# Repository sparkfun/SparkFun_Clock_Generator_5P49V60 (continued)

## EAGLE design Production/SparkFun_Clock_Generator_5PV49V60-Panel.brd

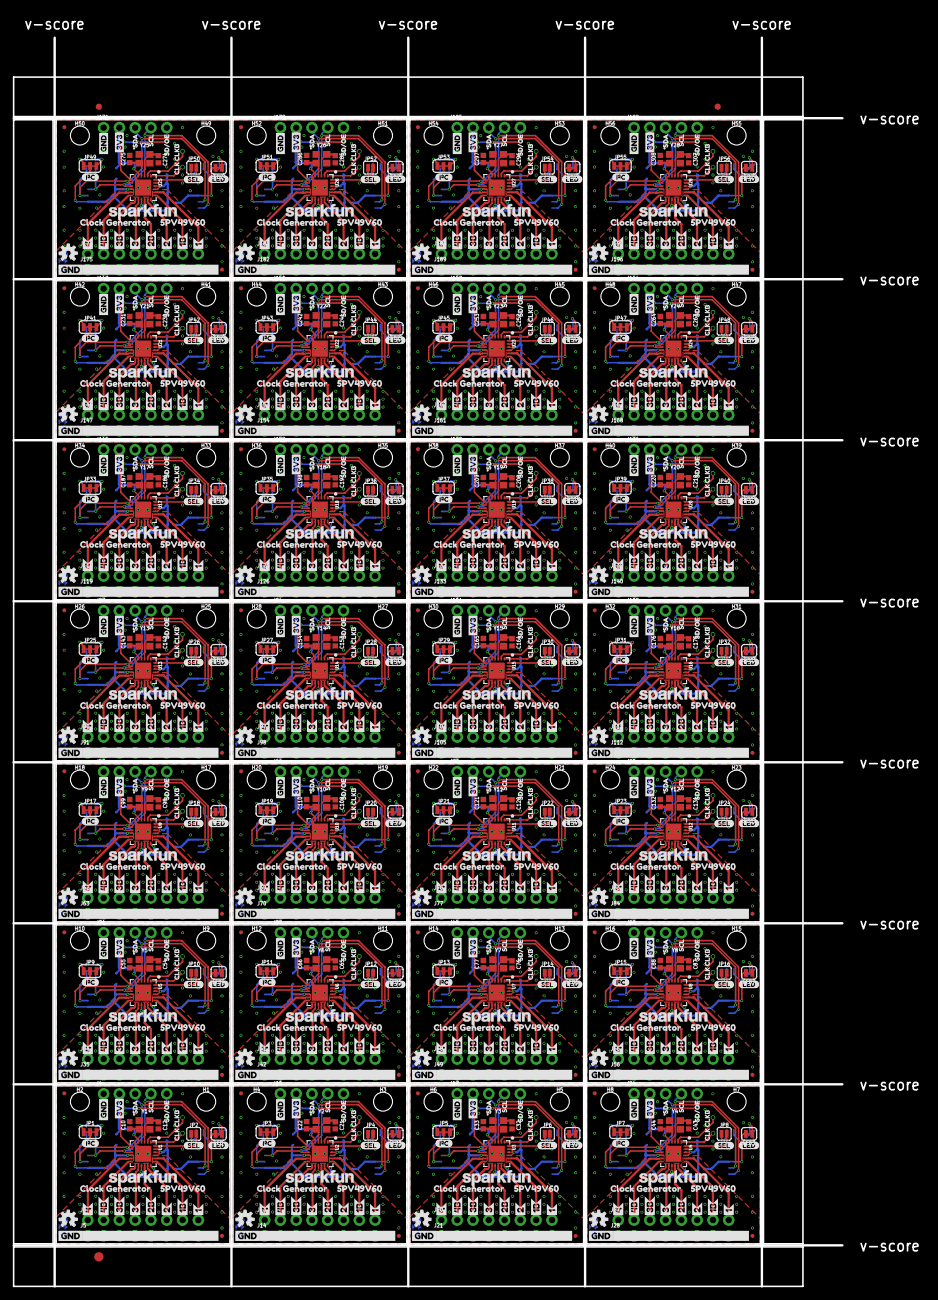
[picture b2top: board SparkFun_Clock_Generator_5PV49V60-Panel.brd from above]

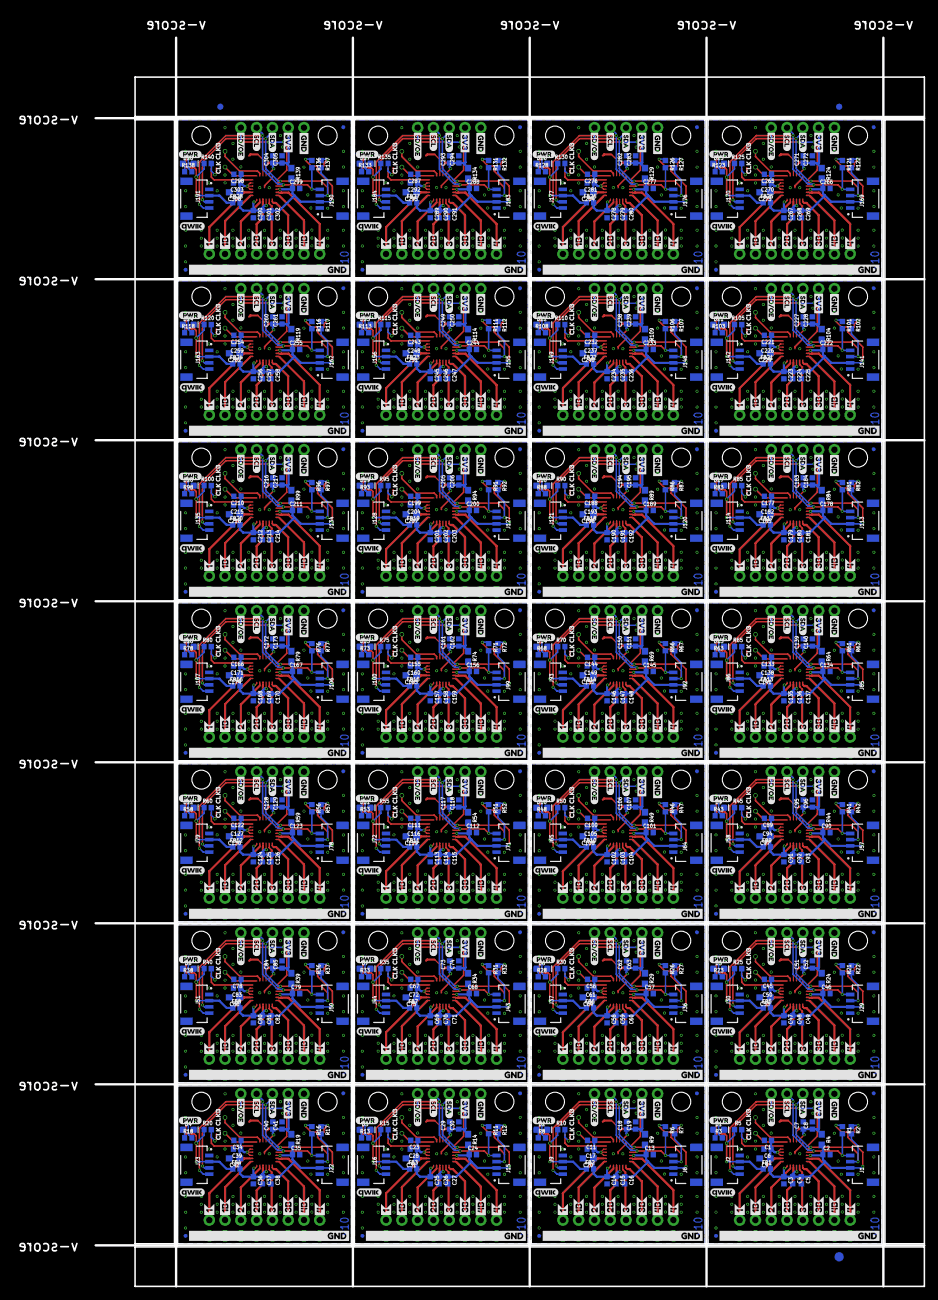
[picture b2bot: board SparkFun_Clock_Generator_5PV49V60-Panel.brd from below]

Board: 2 copper layers, 133.3 x 200.9 mm, 2162 parts (1067 on the bottom side), 644 nets.

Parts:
C1, C2, C3, C4, C5, C6, C7, C11, C13, C14, C15, C16, C17, C18, C23, C24, C25, C26, C27, C28, C29, C34, C35, C36, C37, C38, C39, C40, C45, C46, C47, C48, C49, C50, C51, C56, C57, C58, C59, C60, C61, C62, C67, C68, C69, C70, C71, C72, C73, C78, C79, C80, C81, C82, C83, C84, C89, C90, C91, C92, C93, C94, C95, C100, C101, C102, C103, C104, C105, C106, C111, C112, C113, C114, C115, C116, C117, C122, C123, C124, C125, C126, C127, C128, C133, C134, C135, C136, C137, C138, C139, C144, C145, C146, C147, C148, C149, C150, C155, C156, C157, C158, C159, C160, C161, C166, C167, C168, C169, C170, C171, C172, C177, C178, C179, C180, C181, C182, C183, C188, C189, C190, C191, C192, C193, C194, C199, C200, C201, C202, C203, C204, C205, C210, C211, C212, C213, C214, C215, C216, C221, C222, C223, C224, C225, C226, C227, C232, C233, C234, C235, C236, C237, C238, C243, C244, C245, C246, C247, C248, C249, C254, C255, C256, C257, C258, C259, C260, C265, C266, C267, C268, C269, C270, C271, C276, C277, C278, C279, C280, C281, C282, C287, C288, C289, C290, C291, C292, C293, C298, C299, C300, C301, C302, C303, C304: 0.1uF; 0402
C8, C19, C30, C41, C52, C63, C74, C85, C96, C107, C118, C129, C140, C151, C162, C173, C184, C195, C206, C217, C228, C239, C250, C261, C272, C283, C294, C305: 1.0uF; 0402
C9, C20, C31, C42, C53, C64, C75, C86, C97, C108, C119, C130, C141, C152, C163, C174, C185, C196, C207, C218, C229, C240, C251, C262, C273, C284, C295, C306: 10uF; 0603
C10, C12, C21, C22, C32, C33, C43, C44, C54, C55, C65, C66, C76, C77, C87, C88, C98, C99, C109, C110, C120, C121, C131, C132, C142, C143, C153, C154, C164, C165, C175, C176, C186, C187, C197, C198, C208, C209, C219, C220, C230, C231, C241, C242, C252, C253, C263, C264, C274, C275, C285, C286, C296, C297, C307, C308: 12pF; 0402
D1, D2, D3, D4, D5, D6, D7, D8, D9, D10, D11, D12, D13, D14, D15, D16, D17, D18, D19, D20, D21, D22, D23, D24, D25, D26, D27, D28: RED; LED-0603
E$1, E$2, E$3, E$4: FIDUCIAL-1X2
E$5, E$6: FIDUCIAL-1.5X3
FB1, FB2, FB3, FB4, FB5, FB6, FB7, FB8, FB9, FB10, FB11, FB12, FB13, FB14, FB15, FB16, FB17, FB18, FB19, FB20, FB21, FB22, FB23, FB24, FB25, FB26, FB27, FB28: FERRITE_BEAD-120_OHM-0402; 0402
FD1, FD2, FD3, FD4, FD5, FD6, FD7, FD8, FD9, FD10, FD11, FD12, FD13, FD14, FD15, FD16, FD17, FD18, FD19, FD20, FD21, FD22, FD23, FD24, FD25, FD26, FD27, FD28, FD29, FD30, FD31, FD32, FD33, FD34, FD35, FD36, FD37, FD38, FD39, FD40, FD41, FD42, FD43, FD44, FD45, FD46, FD47, FD48, FD49, FD50, FD51, FD52, FD53, FD54, FD55, FD56, FD57, FD58, FD59, FD60, FD61, FD62, FD63, FD64, FD65, FD66, FD67, FD68, FD69, FD70, FD71, FD72, FD73, FD74, FD75, FD76, FD77, FD78, FD79, FD80, FD81, FD82, FD83, FD84, FD85, FD86, FD87, FD88, FD89, FD90, FD91, FD92, FD93, FD94, FD95, FD96, FD97, FD98, FD99, FD100, FD101, FD102, FD103, FD104, FD105, FD106, FD107, FD108, FD109, FD110, FD111, FD112: FIDUCIALUFIDUCIAL; FIDUCIAL-MICRO
H1, H2, H3, H4, H5, H6, H7, H8, H9, H10, H11, H12, H13, H14, H15, H16, H17, H18, H19, H20, H21, H22, H23, H24, H25, H26, H27, H28, H29, H30, H31, H32, H33, H34, H35, H36, H37, H38, H39, H40, H41, H42, H43, H44, H45, H46, H47, H48, H49, H50, H51, H52, H53, H54, H55, H56: STAND-OFFTIGHT; STAND-OFF-TIGHT
J1, J2, J6, J9, J15, J16, J22, J23, J29, J30, J36, J37, J43, J44, J50, J51, J57, J58, J64, J65, J71, J72, J78, J79, J85, J86, J92, J93, J99, J100, J106, J107, J113, J114, J120, J121, J127, J128, J134, J135, J141, J142, J148, J149, J155, J156, J162, J163, J169, J170, J176, J177, J183, J184, J190, J191: QWIIC_RIGHT_ANGLE; JST04_1MM_RA
J3, J5, J13, J14, J20, J21, J27, J28, J34, J35, J41, J42, J48, J49, J55, J56, J62, J63, J69, J70, J76, J77, J83, J84, J90, J91, J97, J98, J104, J105, J111, J112, J118, J119, J125, J126, J132, J133, J139, J140, J146, J147, J153, J154, J160, J161, J167, J168, J174, J175, J181, J182, J188, J189, J195, J196: 1X08_NO_SILK
J4, J10, J17, J24, J31, J38, J45, J52, J59, J66, J73, J80, J87, J94, J101, J108, J115, J122, J129, J136, J143, J150, J157, J164, J171, J178, J185, J192: 1X05_NO_SILK
J7, J8, J11, J12, J18, J19, J25, J26, J32, J33, J39, J40, J46, J47, J53, J54, J60, J61, J67, J68, J74, J75, J81, J82, J88, J89, J95, J96, J102, J103, J109, J110, J116, J117, J123, J124, J130, J131, J137, J138, J144, J145, J151, J152, J158, J159, J165, J166, J172, J173, J179, J180, J186, J187, J193, J194: 1X01_SMALL
JP1, JP3, JP5, JP7, JP9, JP11, JP13, JP15, JP17, JP19, JP21, JP23, JP25, JP27, JP29, JP31, JP33, JP35, JP37, JP39, JP41, JP43, JP45, JP47, JP49, JP51, JP53, JP55: JUMPER-SMT_3_2-NC_TRACE_SILK; SMT-JUMPER_3_2-NC_TRACE_SILK
JP2, JP4, JP6, JP8, JP10, JP12, JP14, JP16, JP18, JP20, JP22, JP24, JP26, JP28, JP30, JP32, JP34, JP36, JP38, JP40, JP42, JP44, JP46, JP48, JP50, JP52, JP54, JP56: JUMPER-SMT_2_NO_SILK; SMT-JUMPER_2_NO_SILK
LED, LED1, LED2, LED3, LED4, LED5, LED6, LED7, LED8, LED9, LED10, LED11, LED12, LED13, LED14, LED15, LED16, LED17, LED18, LED19, LED20, LED21, LED22, LED23, LED24, LED25, LED26, LED27: JUMPER-SMT_2_NC_TRACE_SILK; SMT-JUMPER_2_NC_TRACE_SILK
LOGO1, LOGO4, LOGO7, LOGO10, LOGO13, LOGO16, LOGO19, LOGO22, LOGO25, LOGO28, LOGO31, LOGO34, LOGO37, LOGO40, LOGO43, LOGO46, LOGO49, LOGO52, LOGO55, LOGO58, LOGO61, LOGO64, LOGO67, LOGO70, LOGO73, LOGO76, LOGO79, LOGO82: SFE_LOGO_NAME.1_INCH; SFE_LOGO_NAME_.1
LOGO2, LOGO5, LOGO8, LOGO11, LOGO14, LOGO17, LOGO20, LOGO23, LOGO26, LOGO29, LOGO32, LOGO35, LOGO38, LOGO41, LOGO44, LOGO47, LOGO50, LOGO53, LOGO56, LOGO59, LOGO62, LOGO65, LOGO68, LOGO71, LOGO74, LOGO77, LOGO80, LOGO83: OSHW-LOGOS; OSHW-LOGO-S
LOGO3, LOGO6, LOGO9, LOGO12, LOGO15, LOGO18, LOGO21, LOGO24, LOGO27, LOGO30, LOGO33, LOGO36, LOGO39, LOGO42, LOGO45, LOGO48, LOGO51, LOGO54, LOGO57, LOGO60, LOGO63, LOGO66, LOGO69, LOGO72, LOGO75, LOGO78, LOGO81, LOGO84: QWIIC_LOGO_4MM; QWIIC_4MM
R1, R2, R5, R6, R7, R10, R11, R12, R15, R16, R17, R20, R21, R22, R25, R26, R27, R30, R31, R32, R35, R36, R37, R40, R41, R42, R45, R46, R47, R50, R51, R52, R55, R56, R57, R60, R61, R62, R65, R66, R67, R70, R71, R72, R75, R76, R77, R80, R81, R82, R85, R86, R87, R90, R91, R92, R95, R96, R97, R100, R101, R102, R105, R106, R107, R110, R111, R112, R115, R116, R117, R120, R121, R122, R125, R126, R127, R130, R131, R132, R135, R136, R137, R140: 10k; 0402
R3, R8, R13, R18, R23, R28, R33, R38, R43, R48, R53, R58, R63, R68, R73, R78, R83, R88, R93, R98, R103, R108, R113, R118, R123, R128, R133, R138: 1KOHM-0402-1/16W-1%; 0402
R4, R9, R14, R19, R24, R29, R34, R39, R44, R49, R54, R59, R64, R69, R74, R79, R84, R89, R94, R99, R104, R109, R114, R119, R124, R129, R134, R139: 2.2; 0603
U1, U2, U3, U4, U5, U6, U7, U8, U9, U10, U11, U12, U13, U14, U15, U16, U17, U18, U19, U20, U21, U22, U23, U24, U25, U26, U27, U28: IDT_5P49V60_CLOCK_GENERATOR; VFQFPN-24
U$1, U$76, U$114, U$152, U$190, U$228, U$266, U$304, U$342, U$380, U$418, U$456, U$494, U$532, U$570, U$608, U$646, U$684, U$722, U$760, U$798, U$836, U$874, U$912, U$950, U$988, U$1026, U$1064: SEL0
U$2, U$18, U$39, U$47, U$77, U$85, U$115, U$123, U$153, U$161, U$191, U$199, U$229, U$237, U$267, U$275, U$305, U$313, U$343, U$351, U$381, U$389, U$419, U$427, U$457, U$465, U$495, U$503, U$533, U$541, U$571, U$579, U$609, U$617, U$647, U$655, U$685, U$693, U$723, U$731, U$761, U$769, U$799, U$807, U$837, U$845, U$875, U$883, U$913, U$921, U$951, U$959, U$989, U$997, U$1027, U$1035: 3V3-03
U$3, U$19, U$40, U$48, U$78, U$86, U$116, U$124, U$154, U$162, U$192, U$200, U$230, U$238, U$268, U$276, U$306, U$314, U$344, U$352, U$382, U$390, U$420, U$428, U$458, U$466, U$496, U$504, U$534, U$542, U$572, U$580, U$610, U$618, U$648, U$656, U$686, U$694, U$724, U$732, U$762, U$770, U$800, U$808, U$838, U$846, U$876, U$884, U$914, U$922, U$952, U$960, U$990, U$998, U$1028, U$1036: GND-03
U$4, U$41, U$79, U$117, U$155, U$193, U$231, U$269, U$307, U$345, U$383, U$421, U$459, U$497, U$535, U$573, U$611, U$649, U$687, U$725, U$763, U$801, U$839, U$877, U$915, U$953, U$991, U$1029: PWR-()-03
U$5, U$42, U$80, U$118, U$156, U$194, U$232, U$270, U$308, U$346, U$384, U$422, U$460, U$498, U$536, U$574, U$612, U$650, U$688, U$726, U$764, U$802, U$840, U$878, U$916, U$954, U$992, U$1030: SDA11
U$6, U$43, U$81, U$119, U$157, U$195, U$233, U$271, U$309, U$347, U$385, U$423, U$461, U$499, U$537, U$575, U$613, U$651, U$689, U$727, U$765, U$803, U$841, U$879, U$917, U$955, U$993, U$1031: SCL10
U$7, U$44, U$82, U$120, U$158, U$196, U$234, U$272, U$310, U$348, U$386, U$424, U$462, U$500, U$538, U$576, U$614, U$652, U$690, U$728, U$766, U$804, U$842, U$880, U$918, U$956, U$994, U$1032: SD#OE12
U$8, U$38, U$65, U$68, U$103, U$106, U$141, U$144, U$179, U$182, U$217, U$220, U$255, U$258, U$293, U$296, U$331, U$334, U$369, U$372, U$407, U$410, U$445, U$448, U$483, U$486, U$521, U$524, U$559, U$562, U$597, U$600, U$635, U$638, U$673, U$676, U$711, U$714, U$749, U$752, U$787, U$790, U$825, U$828, U$863, U$866, U$901, U$904, U$939, U$942, U$977, U$980, U$1015, U$1018, U$1053, U$1056: 46
U$9, U$25, U$61, U$69, U$99, U$107, U$137, U$145, U$175, U$183, U$213, U$221, U$251, U$259, U$289, U$297, U$327, U$335, U$365, U$373, U$403, U$411, U$441, U$449, U$479, U$487, U$517, U$525, U$555, U$563, U$593, U$601, U$631, U$639, U$669, U$677, U$707, U$715, U$745, U$753, U$783, U$791, U$821, U$829, U$859, U$867, U$897, U$905, U$935, U$943, U$973, U$981, U$1011, U$1019, U$1049, U$1057: 4B7
U$10, U$24, U$60, U$70, U$98, U$108, U$136, U$146, U$174, U$184, U$212, U$222, U$250, U$260, U$288, U$298, U$326, U$336, U$364, U$374, U$402, U$412, U$440, U$450, U$478, U$488, U$516, U$526, U$554, U$564, U$592, U$602, U$630, U$640, U$668, U$678, U$706, U$716, U$744, U$754, U$782, U$792, U$820, U$830, U$858, U$868, U$896, U$906, U$934, U$944, U$972, U$982, U$1010, U$1020, U$1048, U$1058: 3B5
U$11, U$37, U$64, U$71, U$102, U$109, U$140, U$147, U$178, U$185, U$216, U$223, U$254, U$261, U$292, U$299, U$330, U$337, U$368, U$375, U$406, U$413, U$444, U$451, U$482, U$489, U$520, U$527, U$558, U$565, U$596, U$603, U$634, U$641, U$672, U$679, U$710, U$717, U$748, U$755, U$786, U$793, U$824, U$831, U$862, U$869, U$900, U$907, U$938, U$945, U$976, U$983, U$1014, U$1021, U$1052, U$1059: 34
U$12, U$23, U$59, U$72, U$97, U$110, U$135, U$148, U$173, U$186, U$211, U$224, U$249, U$262, U$287, U$300, U$325, U$338, U$363, U$376, U$401, U$414, U$439, U$452, U$477, U$490, U$515, U$528, U$553, U$566, U$591, U$604, U$629, U$642, U$667, U$680, U$705, U$718, U$743, U$756, U$781, U$794, U$819, U$832, U$857, U$870, U$895, U$908, U$933, U$946, U$971, U$984, U$1009, U$1022, U$1047, U$1060: 2B3
U$13, U$27, U$63, U$73, U$101, U$111, U$139, U$149, U$177, U$187, U$215, U$225, U$253, U$263, U$291, U$301, U$329, U$339, U$367, U$377, U$405, U$415, U$443, U$453, U$481, U$491, U$519, U$529, U$557, U$567, U$595, U$605, U$633, U$643, U$671, U$681, U$709, U$719, U$747, U$757, U$785, U$795, U$823, U$833, U$861, U$871, U$899, U$909, U$937, U$947, U$975, U$985, U$1013, U$1023, U$1051, U$1061: 22
U$14, U$22, U$58, U$74, U$96, U$112, U$134, U$150, U$172, U$188, U$210, U$226, U$248, U$264, U$286, U$302, U$324, U$340, U$362, U$378, U$400, U$416, U$438, U$454, U$476, U$492, U$514, U$530, U$552, U$568, U$590, U$606, U$628, U$644, U$666, U$682, U$704, U$720, U$742, U$758, U$780, U$796, U$818, U$834, U$856, U$872, U$894, U$910, U$932, U$948, U$970, U$986, U$1008, U$1024, U$1046, U$1062: 1B1
U$15, U$26, U$62, U$75, U$100, U$113, U$138, U$151, U$176, U$189, U$214, U$227, U$252, U$265, U$290, U$303, U$328, U$341, U$366, U$379, U$404, U$417, U$442, U$455, U$480, U$493, U$518, U$531, U$556, U$569, U$594, U$607, U$632, U$645, U$670, U$683, U$708, U$721, U$746, U$759, U$784, U$797, U$822, U$835, U$860, U$873, U$898, U$911, U$936, U$949, U$974, U$987, U$1012, U$1025, U$1050, U$1063: 10
U$16, U$45, U$83, U$121, U$159, U$197, U$235, U$273, U$311, U$349, U$387, U$425, U$463, U$501, U$539, U$577, U$615, U$653, U$691, U$729, U$767, U$805, U$843, U$881, U$919, U$957, U$995, U$1033: CLOCK_GENERATOR0
U$17, U$46, U$84, U$122, U$160, U$198, U$236, U$274, U$312, U$350, U$388, U$426, U$464, U$502, U$540, U$578, U$616, U$654, U$692, U$730, U$768, U$806, U$844, U$882, U$920, U$958, U$996, U$1034: 5PV49V601
U$20, U$21, U$56, U$57, U$94, U$95, U$132, U$133, U$170, U$171, U$208, U$209, U$246, U$247, U$284, U$285, U$322, U$323, U$360, U$361, U$398, U$399, U$436, U$437, U$474, U$475, U$512, U$513, U$550, U$551, U$588, U$589, U$626, U$627, U$664, U$665, U$702, U$703, U$740, U$741, U$778, U$779, U$816, U$817, U$854, U$855, U$892, U$893, U$930, U$931, U$968, U$969, U$1006, U$1007, U$1044, U$1045: GND-04
U$28, U$49, U$87, U$125, U$163, U$201, U$239, U$277, U$315, U$353, U$391, U$429, U$467, U$505, U$543, U$581, U$619, U$657, U$695, U$733, U$771, U$809, U$847, U$885, U$923, U$961, U$999, U$1037: SCL1
U$29, U$50, U$88, U$126, U$164, U$202, U$240, U$278, U$316, U$354, U$392, U$430, U$468, U$506, U$544, U$582, U$620, U$658, U$696, U$734, U$772, U$810, U$848, U$886, U$924, U$962, U$1000, U$1038: SD#OE2
U$30, U$51, U$89, U$127, U$165, U$203, U$241, U$279, U$317, U$355, U$393, U$431, U$469, U$507, U$545, U$583, U$621, U$659, U$697, U$735, U$773, U$811, U$849, U$887, U$925, U$963, U$1001, U$1039: SDA0
U$31, U$33, U$52, U$66, U$90, U$104, U$128, U$142, U$166, U$180, U$204, U$218, U$242, U$256, U$280, U$294, U$318, U$332, U$356, U$370, U$394, U$408, U$432, U$446, U$470, U$484, U$508, U$522, U$546, U$560, U$584, U$598, U$622, U$636, U$660, U$674, U$698, U$712, U$736, U$750, U$774, U$788, U$812, U$826, U$850, U$864, U$888, U$902, U$926, U$940, U$964, U$978, U$1002, U$1016, U$1040, U$1054: CLK12
U$32, U$34, U$53, U$67, U$91, U$105, U$129, U$143, U$167, U$181, U$205, U$219, U$243, U$257, U$281, U$295, U$319, U$333, U$357, U$371, U$395, U$409, U$433, U$447, U$471, U$485, U$509, U$523, U$547, U$561, U$585, U$599, U$623, U$637, U$661, U$675, U$699, U$713, U$737, U$751, U$775, U$789, U$813, U$827, U$851, U$865, U$889, U$903, U$927, U$941, U$965, U$979, U$1003, U$1017, U$1041, U$1055: CLKB13
U$35, U$54, U$92, U$130, U$168, U$206, U$244, U$282, U$320, U$358, U$396, U$434, U$472, U$510, U$548, U$586, U$624, U$662, U$700, U$738, U$776, U$814, U$852, U$890, U$928, U$966, U$1004, U$1042: I_SUPER2_C-()-03
U$36, U$55, U$93, U$131, U$169, U$207, U$245, U$283, U$321, U$359, U$397, U$435, U$473, U$511, U$549, U$587, U$625, U$663, U$701, U$739, U$777, U$815, U$853, U$891, U$929, U$967, U$1005, U$1043: LED0
Y1, Y2, Y3, Y4, Y5, Y6, Y7, Y8, Y9, Y10, Y11, Y12, Y13, Y14, Y15, Y16, Y17, Y18, Y19, Y20, Y21, Y22, Y23, Y24, Y25, Y26, Y27, Y28: 16MHz; CRYSTAL-SMD-2X2.5MM

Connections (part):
3.3V: C1.1, C2.1, C3.1, C4.1, C5.1, C6.1, C7.1, C8.1, C9.1, FB1.1, FB1.2, J1.2, J2.2, J4.2, JP1.2, LED.2, R4.1, R4.2, R5.1, U1.P5, U1.P10, U1.P15, U1.P18, U1.P21, U1.P22, U1.P23
3.3V1: C11.1, C13.1, C14.1, C15.1, C16.1, C17.1, C18.1, C19.1, C20.1, FB2.1, FB2.2, J6.2, J9.2, J10.2, JP3.2, LED1.2, R9.1, R9.2, R10.1, U2.P5, U2.P10, U2.P15, U2.P18, U2.P21, U2.P22, U2.P23
3.3V2: C23.1, C24.1, C25.1, C26.1, C27.1, C28.1, C29.1, C30.1, C31.1, FB3.1, FB3.2, J15.2, J16.2, J17.2, JP5.2, LED2.2, R14.1, R14.2, R15.1, U3.P5, U3.P10, U3.P15, U3.P18, U3.P21, U3.P22, U3.P23
3.3V3: C34.1, C35.1, C36.1, C37.1, C38.1, C39.1, C40.1, C41.1, C42.1, FB4.1, FB4.2, J22.2, J23.2, J24.2, JP7.2, LED3.2, R19.1, R19.2, R20.1, U4.P5, U4.P10, U4.P15, U4.P18, U4.P21, U4.P22, U4.P23
3.3V4: C45.1, C46.1, C47.1, C48.1, C49.1, C50.1, C51.1, C52.1, C53.1, FB5.1, FB5.2, J29.2, J30.2, J31.2, JP9.2, LED4.2, R24.1, R24.2, R25.1, U5.P5, U5.P10, U5.P15, U5.P18, U5.P21, U5.P22, U5.P23
3.3V5: C56.1, C57.1, C58.1, C59.1, C60.1, C61.1, C62.1, C63.1, C64.1, FB6.1, FB6.2, J36.2, J37.2, J38.2, JP11.2, LED5.2, R29.1, R29.2, R30.1, U6.P5, U6.P10, U6.P15, U6.P18, U6.P21, U6.P22, U6.P23
3.3V6: C67.1, C68.1, C69.1, C70.1, C71.1, C72.1, C73.1, C74.1, C75.1, FB7.1, FB7.2, J43.2, J44.2, J45.2, JP13.2, LED6.2, R34.1, R34.2, R35.1, U7.P5, U7.P10, U7.P15, U7.P18, U7.P21, U7.P22, U7.P23
3.3V7: C78.1, C79.1, C80.1, C81.1, C82.1, C83.1, C84.1, C85.1, C86.1, FB8.1, FB8.2, J50.2, J51.2, J52.2, JP15.2, LED7.2, R39.1, R39.2, R40.1, U8.P5, U8.P10, U8.P15, U8.P18, U8.P21, U8.P22, U8.P23
3.3V8: C89.1, C90.1, C91.1, C92.1, C93.1, C94.1, C95.1, C96.1, C97.1, FB9.1, FB9.2, J57.2, J58.2, J59.2, JP17.2, LED8.2, R44.1, R44.2, R45.1, U9.P5, U9.P10, U9.P15, U9.P18, U9.P21, U9.P22, U9.P23
3.3V9: C100.1, C101.1, C102.1, C103.1, C104.1, C105.1, C106.1, C107.1, C108.1, FB10.1, FB10.2, J64.2, J65.2, J66.2, JP19.2, LED9.2, R49.1, R49.2, R50.1, U10.P5, U10.P10, U10.P15, U10.P18, U10.P21, U10.P22, U10.P23
3.3V10: C111.1, C112.1, C113.1, C114.1, C115.1, C116.1, C117.1, C118.1, C119.1, FB11.1, FB11.2, J71.2, J72.2, J73.2, JP21.2, LED10.2, R54.1, R54.2, R55.1, U11.P5, U11.P10, U11.P15, U11.P18, U11.P21, U11.P22, U11.P23
3.3V11: C122.1, C123.1, C124.1, C125.1, C126.1, C127.1, C128.1, C129.1, C130.1, FB12.1, FB12.2, J78.2, J79.2, J80.2, JP23.2, LED11.2, R59.1, R59.2, R60.1, U12.P5, U12.P10, U12.P15, U12.P18, U12.P21, U12.P22, U12.P23
3.3V12: C133.1, C134.1, C135.1, C136.1, C137.1, C138.1, C139.1, C140.1, C141.1, FB13.1, FB13.2, J85.2, J86.2, J87.2, JP25.2, LED12.2, R64.1, R64.2, R65.1, U13.P5, U13.P10, U13.P15, U13.P18, U13.P21, U13.P22, U13.P23
3.3V13: C144.1, C145.1, C146.1, C147.1, C148.1, C149.1, C150.1, C151.1, C152.1, FB14.1, FB14.2, J92.2, J93.2, J94.2, JP27.2, LED13.2, R69.1, R69.2, R70.1, U14.P5, U14.P10, U14.P15, U14.P18, U14.P21, U14.P22, U14.P23
3.3V14: C155.1, C156.1, C157.1, C158.1, C159.1, C160.1, C161.1, C162.1, C163.1, FB15.1, FB15.2, J99.2, J100.2, J101.2, JP29.2, LED14.2, R74.1, R74.2, R75.1, U15.P5, U15.P10, U15.P15, U15.P18, U15.P21, U15.P22, U15.P23
3.3V15: C166.1, C167.1, C168.1, C169.1, C170.1, C171.1, C172.1, C173.1, C174.1, FB16.1, FB16.2, J106.2, J107.2, J108.2, JP31.2, LED15.2, R79.1, R79.2, R80.1, U16.P5, U16.P10, U16.P15, U16.P18, U16.P21, U16.P22, U16.P23
3.3V16: C177.1, C178.1, C179.1, C180.1, C181.1, C182.1, C183.1, C184.1, C185.1, FB17.1, FB17.2, J113.2, J114.2, J115.2, JP33.2, LED16.2, R84.1, R84.2, R85.1, U17.P5, U17.P10, U17.P15, U17.P18, U17.P21, U17.P22, U17.P23
3.3V17: C188.1, C189.1, C190.1, C191.1, C192.1, C193.1, C194.1, C195.1, C196.1, FB18.1, FB18.2, J120.2, J121.2, J122.2, JP35.2, LED17.2, R89.1, R89.2, R90.1, U18.P5, U18.P10, U18.P15, U18.P18, U18.P21, U18.P22, U18.P23
3.3V18: C199.1, C200.1, C201.1, C202.1, C203.1, C204.1, C205.1, C206.1, C207.1, FB19.1, FB19.2, J127.2, J128.2, J129.2, JP37.2, LED18.2, R94.1, R94.2, R95.1, U19.P5, U19.P10, U19.P15, U19.P18, U19.P21, U19.P22, U19.P23
3.3V19: C210.1, C211.1, C212.1, C213.1, C214.1, C215.1, C216.1, C217.1, C218.1, FB20.1, FB20.2, J134.2, J135.2, J136.2, JP39.2, LED19.2, R99.1, R99.2, R100.1, U20.P5, U20.P10, U20.P15, U20.P18, U20.P21, U20.P22, U20.P23
3.3V20: C221.1, C222.1, C223.1, C224.1, C225.1, C226.1, C227.1, C228.1, C229.1, FB21.1, FB21.2, J141.2, J142.2, J143.2, JP41.2, LED20.2, R104.1, R104.2, R105.1, U21.P5, U21.P10, U21.P15, U21.P18, U21.P21, U21.P22, U21.P23
3.3V21: C232.1, C233.1, C234.1, C235.1, C236.1, C237.1, C238.1, C239.1, C240.1, FB22.1, FB22.2, J148.2, J149.2, J150.2, JP43.2, LED21.2, R109.1, R109.2, R110.1, U22.P5, U22.P10, U22.P15, U22.P18, U22.P21, U22.P22, U22.P23
3.3V22: C243.1, C244.1, C245.1, C246.1, C247.1, C248.1, C249.1, C250.1, C251.1, FB23.1, FB23.2, J155.2, J156.2, J157.2, JP45.2, LED22.2, R114.1, R114.2, R115.1, U23.P5, U23.P10, U23.P15, U23.P18, U23.P21, U23.P22, U23.P23
3.3V23: C254.1, C255.1, C256.1, C257.1, C258.1, C259.1, C260.1, C261.1, C262.1, FB24.1, FB24.2, J162.2, J163.2, J164.2, JP47.2, LED23.2, R119.1, R119.2, R120.1, U24.P5, U24.P10, U24.P15, U24.P18, U24.P21, U24.P22, U24.P23
3.3V24: C265.1, C266.1, C267.1, C268.1, C269.1, C270.1, C271.1, C272.1, C273.1, FB25.1, FB25.2, J169.2, J170.2, J171.2, JP49.2, LED24.2, R124.1, R124.2, R125.1, U25.P5, U25.P10, U25.P15, U25.P18, U25.P21, U25.P22, U25.P23
3.3V25: C276.1, C277.1, C278.1, C279.1, C280.1, C281.1, C282.1, C283.1, C284.1, FB26.1, FB26.2, J176.2, J177.2, J178.2, JP51.2, LED25.2, R129.1, R129.2, R130.1, U26.P5, U26.P10, U26.P15, U26.P18, U26.P21, U26.P22, U26.P23
3.3V26: C287.1, C288.1, C289.1, C290.1, C291.1, C292.1, C293.1, C294.1, C295.1, FB27.1, FB27.2, J183.2, J184.2, J185.2, JP53.2, LED26.2, R134.1, R134.2, R135.1, U27.P5, U27.P10, U27.P15, U27.P18, U27.P21, U27.P22, U27.P23
3.3V27: C298.1, C299.1, C300.1, C301.1, C302.1, C303.1, C304.1, C305.1, C306.1, FB28.1, FB28.2, J190.2, J191.2, J192.2, JP55.2, LED27.2, R139.1, R139.2, R140.1, U28.P5, U28.P10, U28.P15, U28.P18, U28.P21, U28.P22, U28.P23
CLKIN: J8.P$1, U1.P1
CLKIN1: J12.P$1, U2.P1
CLKIN2: J19.P$1, U3.P1
CLKIN3: J26.P$1, U4.P1
CLKIN4: J33.P$1, U5.P1
CLKIN5: J40.P$1, U6.P1
CLKIN6: J47.P$1, U7.P1
CLKIN7: J54.P$1, U8.P1
CLKIN8: J61.P$1, U9.P1
CLKIN9: J68.P$1, U10.P1
CLKIN10: J75.P$1, U11.P1
CLKIN11: J82.P$1, U12.P1
CLKIN12: J89.P$1, U13.P1
CLKIN13: J96.P$1, U14.P1
CLKIN14: J103.P$1, U15.P1
CLKIN15: J110.P$1, U16.P1
CLKIN16: J117.P$1, U17.P1
CLKIN17: J124.P$1, U18.P1
CLKIN18: J131.P$1, U19.P1
CLKIN19: J138.P$1, U20.P1
CLKIN20: J145.P$1, U21.P1
CLKIN21: J152.P$1, U22.P1
CLKIN22: J159.P$1, U23.P1
CLKIN23: J166.P$1, U24.P1
CLKIN24: J173.P$1, U25.P1
CLKIN25: J180.P$1, U26.P1
CLKIN26: J187.P$1, U27.P1
CLKIN27: J194.P$1, U28.P1
CLKINB: J7.P$1, U1.P2
CLKINB1: J11.P$1, U2.P2
CLKINB2: J18.P$1, U3.P2
CLKINB3: J25.P$1, U4.P2
CLKINB4: J32.P$1, U5.P2
CLKINB5: J39.P$1, U6.P2
CLKINB6: J46.P$1, U7.P2
CLKINB7: J53.P$1, U8.P2
CLKINB8: J60.P$1, U9.P2
CLKINB9: J67.P$1, U10.P2
CLKINB10: J74.P$1, U11.P2
CLKINB11: J81.P$1, U12.P2
CLKINB12: J88.P$1, U13.P2
CLKINB13: J95.P$1, U14.P2
CLKINB14: J102.P$1, U15.P2
CLKINB15: J109.P$1, U16.P2
CLKINB16: J116.P$1, U17.P2
CLKINB17: J123.P$1, U18.P2
CLKINB18: J130.P$1, U19.P2
CLKINB19: J137.P$1, U20.P2
CLKINB20: J144.P$1, U21.P2
CLKINB21: J151.P$1, U22.P2
CLKINB22: J158.P$1, U23.P2
CLKINB23: J165.P$1, U24.P2
CLKINB24: J172.P$1, U25.P2
CLKINB25: J179.P$1, U26.P2
CLKINB26: J186.P$1, U27.P2
CLKINB27: J193.P$1, U28.P2
GND: C1.2, C2.2, C3.2, C4.2, C5.2, C6.2, C7.2, C8.2, C9.2, C10.2, C12.2, D1.C, J1.1, J2.1, J4.1, J5.1, J5.2, J5.3, J5.4, J5.5, J5.6, J5.7, J5.8, U1.GND, U1.P6, Y1.P2, Y1.P4
GND1: C11.2, C13.2, C14.2, C15.2, C16.2, C17.2, C18.2, C19.2, C20.2, C21.2, C22.2, D2.C, J6.1, J9.1, J10.1, J14.1, J14.2, J14.3, J14.4, J14.5, J14.6, J14.7, J14.8, U2.GND, U2.P6, Y2.P2, Y2.P4
GND2: C23.2, C24.2, C25.2, C26.2, C27.2, C28.2, C29.2, C30.2, C31.2, C32.2, C33.2, D3.C, J15.1, J16.1, J17.1, J21.1, J21.2, J21.3, J21.4, J21.5, J21.6, J21.7, J21.8, U3.GND, U3.P6, Y3.P2, Y3.P4
GND3: C34.2, C35.2, C36.2, C37.2, C38.2, C39.2, C40.2, C41.2, C42.2, C43.2, C44.2, D4.C, J22.1, J23.1, J24.1, J28.1, J28.2, J28.3, J28.4, J28.5, J28.6, J28.7, J28.8, U4.GND, U4.P6, Y4.P2, Y4.P4
GND4: C45.2, C46.2, C47.2, C48.2, C49.2, C50.2, C51.2, C52.2, C53.2, C54.2, C55.2, D5.C, J29.1, J30.1, J31.1, J35.1, J35.2, J35.3, J35.4, J35.5, J35.6, J35.7, J35.8, U5.GND, U5.P6, Y5.P2, Y5.P4
GND5: C56.2, C57.2, C58.2, C59.2, C60.2, C61.2, C62.2, C63.2, C64.2, C65.2, C66.2, D6.C, J36.1, J37.1, J38.1, J42.1, J42.2, J42.3, J42.4, J42.5, J42.6, J42.7, J42.8, U6.GND, U6.P6, Y6.P2, Y6.P4
GND6: C67.2, C68.2, C69.2, C70.2, C71.2, C72.2, C73.2, C74.2, C75.2, C76.2, C77.2, D7.C, J43.1, J44.1, J45.1, J49.1, J49.2, J49.3, J49.4, J49.5, J49.6, J49.7, J49.8, U7.GND, U7.P6, Y7.P2, Y7.P4
GND7: C78.2, C79.2, C80.2, C81.2, C82.2, C83.2, C84.2, C85.2, C86.2, C87.2, C88.2, D8.C, J50.1, J51.1, J52.1, J56.1, J56.2, J56.3, J56.4, J56.5, J56.6, J56.7, J56.8, U8.GND, U8.P6, Y8.P2, Y8.P4
GND8: C89.2, C90.2, C91.2, C92.2, C93.2, C94.2, C95.2, C96.2, C97.2, C98.2, C99.2, D9.C, J57.1, J58.1, J59.1, J63.1, J63.2, J63.3, J63.4, J63.5, J63.6, J63.7, J63.8, U9.GND, U9.P6, Y9.P2, Y9.P4
GND9: C100.2, C101.2, C102.2, C103.2, C104.2, C105.2, C106.2, C107.2, C108.2, C109.2, C110.2, D10.C, J64.1, J65.1, J66.1, J70.1, J70.2, J70.3, J70.4, J70.5, J70.6, J70.7, J70.8, U10.GND, U10.P6, Y10.P2, Y10.P4
GND10: C111.2, C112.2, C113.2, C114.2, C115.2, C116.2, C117.2, C118.2, C119.2, C120.2, C121.2, D11.C, J71.1, J72.1, J73.1, J77.1, J77.2, J77.3, J77.4, J77.5, J77.6, J77.7, J77.8, U11.GND, U11.P6, Y11.P2, Y11.P4
GND11: C122.2, C123.2, C124.2, C125.2, C126.2, C127.2, C128.2, C129.2, C130.2, C131.2, C132.2, D12.C, J78.1, J79.1, J80.1, J84.1, J84.2, J84.3, J84.4, J84.5, J84.6, J84.7, J84.8, U12.GND, U12.P6, Y12.P2, Y12.P4
GND12: C133.2, C134.2, C135.2, C136.2, C137.2, C138.2, C139.2, C140.2, C141.2, C142.2, C143.2, D13.C, J85.1, J86.1, J87.1, J91.1, J91.2, J91.3, J91.4, J91.5, J91.6, J91.7, J91.8, U13.GND, U13.P6, Y13.P2, Y13.P4
GND13: C144.2, C145.2, C146.2, C147.2, C148.2, C149.2, C150.2, C151.2, C152.2, C153.2, C154.2, D14.C, J92.1, J93.1, J94.1, J98.1, J98.2, J98.3, J98.4, J98.5, J98.6, J98.7, J98.8, U14.GND, U14.P6, Y14.P2, Y14.P4
GND14: C155.2, C156.2, C157.2, C158.2, C159.2, C160.2, C161.2, C162.2, C163.2, C164.2, C165.2, D15.C, J99.1, J100.1, J101.1, J105.1, J105.2, J105.3, J105.4, J105.5, J105.6, J105.7, J105.8, U15.GND, U15.P6, Y15.P2, Y15.P4
GND15: C166.2, C167.2, C168.2, C169.2, C170.2, C171.2, C172.2, C173.2, C174.2, C175.2, C176.2, D16.C, J106.1, J107.1, J108.1, J112.1, J112.2, J112.3, J112.4, J112.5, J112.6, J112.7, J112.8, U16.GND, U16.P6, Y16.P2, Y16.P4
GND16: C177.2, C178.2, C179.2, C180.2, C181.2, C182.2, C183.2, C184.2, C185.2, C186.2, C187.2, D17.C, J113.1, J114.1, J115.1, J119.1, J119.2, J119.3, J119.4, J119.5, J119.6, J119.7, J119.8, U17.GND, U17.P6, Y17.P2, Y17.P4
GND17: C188.2, C189.2, C190.2, C191.2, C192.2, C193.2, C194.2, C195.2, C196.2, C197.2, C198.2, D18.C, J120.1, J121.1, J122.1, J126.1, J126.2, J126.3, J126.4, J126.5, J126.6, J126.7, J126.8, U18.GND, U18.P6, Y18.P2, Y18.P4
GND18: C199.2, C200.2, C201.2, C202.2, C203.2, C204.2, C205.2, C206.2, C207.2, C208.2, C209.2, D19.C, J127.1, J128.1, J129.1, J133.1, J133.2, J133.3, J133.4, J133.5, J133.6, J133.7, J133.8, U19.GND, U19.P6, Y19.P2, Y19.P4
GND19: C210.2, C211.2, C212.2, C213.2, C214.2, C215.2, C216.2, C217.2, C218.2, C219.2, C220.2, D20.C, J134.1, J135.1, J136.1, J140.1, J140.2, J140.3, J140.4, J140.5, J140.6, J140.7, J140.8, U20.GND, U20.P6, Y20.P2, Y20.P4
GND20: C221.2, C222.2, C223.2, C224.2, C225.2, C226.2, C227.2, C228.2, C229.2, C230.2, C231.2, D21.C, J141.1, J142.1, J143.1, J147.1, J147.2, J147.3, J147.4, J147.5, J147.6, J147.7, J147.8, U21.GND, U21.P6, Y21.P2, Y21.P4
GND21: C232.2, C233.2, C234.2, C235.2, C236.2, C237.2, C238.2, C239.2, C240.2, C241.2, C242.2, D22.C, J148.1, J149.1, J150.1, J154.1, J154.2, J154.3, J154.4, J154.5, J154.6, J154.7, J154.8, U22.GND, U22.P6, Y22.P2, Y22.P4
GND22: C243.2, C244.2, C245.2, C246.2, C247.2, C248.2, C249.2, C250.2, C251.2, C252.2, C253.2, D23.C, J155.1, J156.1, J157.1, J161.1, J161.2, J161.3, J161.4, J161.5, J161.6, J161.7, J161.8, U23.GND, U23.P6, Y23.P2, Y23.P4
GND23: C254.2, C255.2, C256.2, C257.2, C258.2, C259.2, C260.2, C261.2, C262.2, C263.2, C264.2, D24.C, J162.1, J163.1, J164.1, J168.1, J168.2, J168.3, J168.4, J168.5, J168.6, J168.7, J168.8, U24.GND, U24.P6, Y24.P2, Y24.P4
GND24: C265.2, C266.2, C267.2, C268.2, C269.2, C270.2, C271.2, C272.2, C273.2, C274.2, C275.2, D25.C, J169.1, J170.1, J171.1, J175.1, J175.2, J175.3, J175.4, J175.5, J175.6, J175.7, J175.8, U25.GND, U25.P6, Y25.P2, Y25.P4
GND25: C276.2, C277.2, C278.2, C279.2, C280.2, C281.2, C282.2, C283.2, C284.2, C285.2, C286.2, D26.C, J176.1, J177.1, J178.1, J182.1, J182.2, J182.3, J182.4, J182.5, J182.6, J182.7, J182.8, U26.GND, U26.P6, Y26.P2, Y26.P4
GND26: C287.2, C288.2, C289.2, C290.2, C291.2, C292.2, C293.2, C294.2, C295.2, C296.2, C297.2, D27.C, J183.1, J184.1, J185.1, J189.1, J189.2, J189.3, J189.4, J189.5, J189.6, J189.7, J189.8, U27.GND, U27.P6, Y27.P2, Y27.P4
GND27: C298.2, C299.2, C300.2, C301.2, C302.2, C303.2, C304.2, C305.2, C306.2, C307.2, C308.2, D28.C, J190.1, J191.1, J192.1, J196.1, J196.2, J196.3, J196.4, J196.5, J196.6, J196.7, J196.8, U28.GND, U28.P6, Y28.P2, Y28.P4
unnamed: JP1.1, R2.1
unnamed: C12.1, U1.P3, Y1.P1
unnamed: JP1.3, R1.1
unnamed: LED.1, R3.2
unnamed: D1.A, R3.1
unnamed: C10.1, U1.P4, Y1.P3
unnamed: JP2.1, R5.2
unnamed: JP3.1, R7.1
unnamed: JP3.3, R6.1
unnamed: C22.1, U2.P4, Y2.P3
unnamed: C21.1, U2.P3, Y2.P1
unnamed: LED1.1, R8.2
unnamed: D2.A, R8.1
unnamed: JP4.1, R10.2
unnamed: JP5.1, R12.1
unnamed: JP5.3, R11.1
unnamed: C33.1, U3.P4, Y3.P3
unnamed: C32.1, U3.P3, Y3.P1
unnamed: LED2.1, R13.2
unnamed: D3.A, R13.1
unnamed: JP6.1, R15.2
unnamed: JP7.1, R17.1
unnamed: JP7.3, R16.1
unnamed: C44.1, U4.P4, Y4.P3
unnamed: C43.1, U4.P3, Y4.P1
unnamed: LED3.1, R18.2
unnamed: D4.A, R18.1
unnamed: JP8.1, R20.2
unnamed: JP9.1, R22.1
unnamed: JP9.3, R21.1
unnamed: C55.1, U5.P4, Y5.P3
unnamed: C54.1, U5.P3, Y5.P1
unnamed: LED4.1, R23.2
unnamed: D5.A, R23.1
unnamed: JP10.1, R25.2
unnamed: JP11.1, R27.1
unnamed: JP11.3, R26.1
unnamed: C66.1, U6.P4, Y6.P3
unnamed: C65.1, U6.P3, Y6.P1
unnamed: LED5.1, R28.2
unnamed: D6.A, R28.1
unnamed: JP12.1, R30.2
unnamed: JP13.1, R32.1
unnamed: JP13.3, R31.1
unnamed: C77.1, U7.P4, Y7.P3
unnamed: C76.1, U7.P3, Y7.P1
unnamed: LED6.1, R33.2
unnamed: D7.A, R33.1
unnamed: JP14.1, R35.2
unnamed: JP15.1, R37.1
unnamed: JP15.3, R36.1
unnamed: C88.1, U8.P4, Y8.P3
unnamed: C87.1, U8.P3, Y8.P1
unnamed: LED7.1, R38.2
unnamed: D8.A, R38.1
unnamed: JP16.1, R40.2
unnamed: JP17.1, R42.1
unnamed: JP17.3, R41.1
unnamed: C99.1, U9.P4, Y9.P3
unnamed: C98.1, U9.P3, Y9.P1
unnamed: LED8.1, R43.2
unnamed: D9.A, R43.1
unnamed: JP18.1, R45.2
unnamed: JP19.1, R47.1
unnamed: JP19.3, R46.1
unnamed: C110.1, U10.P4, Y10.P3
unnamed: C109.1, U10.P3, Y10.P1
unnamed: LED9.1, R48.2
unnamed: D10.A, R48.1
unnamed: JP20.1, R50.2
unnamed: JP21.1, R52.1
unnamed: JP21.3, R51.1
unnamed: C121.1, U11.P4, Y11.P3
unnamed: C120.1, U11.P3, Y11.P1
unnamed: LED10.1, R53.2
unnamed: D11.A, R53.1
unnamed: JP22.1, R55.2
unnamed: JP23.1, R57.1
unnamed: JP23.3, R56.1
unnamed: C132.1, U12.P4, Y12.P3
unnamed: C131.1, U12.P3, Y12.P1
unnamed: LED11.1, R58.2
unnamed: D12.A, R58.1
unnamed: JP24.1, R60.2
unnamed: JP25.1, R62.1
unnamed: JP25.3, R61.1
unnamed: C143.1, U13.P4, Y13.P3
unnamed: C142.1, U13.P3, Y13.P1
unnamed: LED12.1, R63.2
unnamed: D13.A, R63.1
unnamed: JP26.1, R65.2
unnamed: JP27.1, R67.1
unnamed: JP27.3, R66.1
unnamed: C154.1, U14.P4, Y14.P3
unnamed: C153.1, U14.P3, Y14.P1
unnamed: LED13.1, R68.2
unnamed: D14.A, R68.1
unnamed: JP28.1, R70.2
unnamed: JP29.1, R72.1
unnamed: JP29.3, R71.1
unnamed: C165.1, U15.P4, Y15.P3
unnamed: C164.1, U15.P3, Y15.P1
unnamed: LED14.1, R73.2
unnamed: D15.A, R73.1
unnamed: JP30.1, R75.2
unnamed: JP31.1, R77.1
unnamed: JP31.3, R76.1
unnamed: C176.1, U16.P4, Y16.P3
unnamed: C175.1, U16.P3, Y16.P1
unnamed: LED15.1, R78.2
unnamed: D16.A, R78.1
unnamed: JP32.1, R80.2
unnamed: JP33.1, R82.1
unnamed: JP33.3, R81.1
unnamed: C187.1, U17.P4, Y17.P3
unnamed: C186.1, U17.P3, Y17.P1
unnamed: LED16.1, R83.2
unnamed: D17.A, R83.1
unnamed: JP34.1, R85.2
unnamed: JP35.1, R87.1
unnamed: JP35.3, R86.1
unnamed: C198.1, U18.P4, Y18.P3
unnamed: C197.1, U18.P3, Y18.P1
unnamed: LED17.1, R88.2
unnamed: D18.A, R88.1
unnamed: JP36.1, R90.2
unnamed: JP37.1, R92.1
unnamed: JP37.3, R91.1
unnamed: C209.1, U19.P4, Y19.P3
unnamed: C208.1, U19.P3, Y19.P1
unnamed: LED18.1, R93.2
unnamed: D19.A, R93.1
unnamed: JP38.1, R95.2
unnamed: JP39.1, R97.1
unnamed: JP39.3, R96.1
unnamed: C220.1, U20.P4, Y20.P3
unnamed: C219.1, U20.P3, Y20.P1
unnamed: LED19.1, R98.2
unnamed: D20.A, R98.1
unnamed: JP40.1, R100.2
unnamed: JP41.1, R102.1
unnamed: JP41.3, R101.1
unnamed: C231.1, U21.P4, Y21.P3
unnamed: C230.1, U21.P3, Y21.P1
unnamed: LED20.1, R103.2
unnamed: D21.A, R103.1
unnamed: JP42.1, R105.2
unnamed: JP43.1, R107.1
unnamed: JP43.3, R106.1
unnamed: C242.1, U22.P4, Y22.P3
unnamed: C241.1, U22.P3, Y22.P1
unnamed: LED21.1, R108.2
unnamed: D22.A, R108.1
unnamed: JP44.1, R110.2
unnamed: JP45.1, R112.1
unnamed: JP45.3, R111.1
unnamed: C253.1, U23.P4, Y23.P3
unnamed: C252.1, U23.P3, Y23.P1
unnamed: LED22.1, R113.2
unnamed: D23.A, R113.1
unnamed: JP46.1, R115.2
unnamed: JP47.1, R117.1
unnamed: JP47.3, R116.1
unnamed: C264.1, U24.P4, Y24.P3
unnamed: C263.1, U24.P3, Y24.P1
unnamed: LED23.1, R118.2
unnamed: D24.A, R118.1
unnamed: JP48.1, R120.2
unnamed: JP49.1, R122.1
unnamed: JP49.3, R121.1
unnamed: C275.1, U25.P4, Y25.P3
unnamed: C274.1, U25.P3, Y25.P1
unnamed: LED24.1, R123.2
unnamed: D25.A, R123.1
unnamed: JP50.1, R125.2
unnamed: JP51.1, R127.1
unnamed: JP51.3, R126.1
unnamed: C286.1, U26.P4, Y26.P3
unnamed: C285.1, U26.P3, Y26.P1
unnamed: LED25.1, R128.2
unnamed: D26.A, R128.1
unnamed: JP52.1, R130.2
unnamed: JP53.1, R132.1
unnamed: JP53.3, R131.1
unnamed: C297.1, U27.P4, Y27.P3
unnamed: C296.1, U27.P3, Y27.P1
unnamed: LED26.1, R133.2
unnamed: D27.A, R133.1
unnamed: JP54.1, R135.2
unnamed: JP55.1, R137.1
unnamed: JP55.3, R136.1
unnamed: C308.1, U28.P4, Y28.P3
unnamed: C307.1, U28.P3, Y28.P1
unnamed: LED27.1, R138.2
unnamed: D28.A, R138.1
unnamed: JP56.1, R140.2
OUT1: J3.8, U1.P20
OUT1B: J3.7, U1.P19
OUT1B1: J13.7, U2.P19
OUT1B2: J20.7, U3.P19
OUT1B3: J27.7, U4.P19
OUT1B4: J34.7, U5.P19
OUT1B5: J41.7, U6.P19
OUT1B6: J48.7, U7.P19
OUT1B7: J55.7, U8.P19
OUT1B8: J62.7, U9.P19
OUT1B9: J69.7, U10.P19
OUT1B10: J76.7, U11.P19
OUT1B11: J83.7, U12.P19
OUT1B12: J90.7, U13.P19
OUT1B13: J97.7, U14.P19
OUT1B14: J104.7, U15.P19
OUT1B15: J111.7, U16.P19
OUT1B16: J118.7, U17.P19
OUT1B17: J125.7, U18.P19
OUT1B18: J132.7, U19.P19
OUT1B19: J139.7, U20.P19
OUT1B20: J146.7, U21.P19
OUT1B21: J153.7, U22.P19
OUT1B22: J160.7, U23.P19
OUT1B23: J167.7, U24.P19
OUT1B24: J174.7, U25.P19
OUT1B25: J181.7, U26.P19
OUT1B26: J188.7, U27.P19
OUT1B27: J195.7, U28.P19
OUT2: J3.6, U1.P17
OUT2B: J3.5, U1.P16
OUT2B1: J13.5, U2.P16
OUT2B2: J20.5, U3.P16
OUT2B3: J27.5, U4.P16
OUT2B4: J34.5, U5.P16
OUT2B5: J41.5, U6.P16
OUT2B6: J48.5, U7.P16
OUT2B7: J55.5, U8.P16
OUT2B8: J62.5, U9.P16
OUT2B9: J69.5, U10.P16
OUT2B10: J76.5, U11.P16
OUT2B11: J83.5, U12.P16
OUT2B12: J90.5, U13.P16
OUT2B13: J97.5, U14.P16
OUT2B14: J104.5, U15.P16
OUT2B15: J111.5, U16.P16
OUT2B16: J118.5, U17.P16
OUT2B17: J125.5, U18.P16
OUT2B18: J132.5, U19.P16
OUT2B19: J139.5, U20.P16
OUT2B20: J146.5, U21.P16
OUT2B21: J153.5, U22.P16
OUT2B22: J160.5, U23.P16
OUT2B23: J167.5, U24.P16
OUT2B24: J174.5, U25.P16
OUT2B25: J181.5, U26.P16
OUT2B26: J188.5, U27.P16
OUT2B27: J195.5, U28.P16
OUT3: J3.4, U1.P14
OUT3B: J3.3, U1.P13
OUT3B1: J13.3, U2.P13
OUT3B2: J20.3, U3.P13
OUT3B3: J27.3, U4.P13
OUT3B4: J34.3, U5.P13
OUT3B5: J41.3, U6.P13
OUT3B6: J48.3, U7.P13
OUT3B7: J55.3, U8.P13
OUT3B8: J62.3, U9.P13
OUT3B9: J69.3, U10.P13
OUT3B10: J76.3, U11.P13
OUT3B11: J83.3, U12.P13
OUT3B12: J90.3, U13.P13
OUT3B13: J97.3, U14.P13
OUT3B14: J104.3, U15.P13
OUT3B15: J111.3, U16.P13
OUT3B16: J118.3, U17.P13
OUT3B17: J125.3, U18.P13
OUT3B18: J132.3, U19.P13
OUT3B19: J139.3, U20.P13
OUT3B20: J146.3, U21.P13
OUT3B21: J153.3, U22.P13
OUT3B22: J160.3, U23.P13
OUT3B23: J167.3, U24.P13
OUT3B24: J174.3, U25.P13
OUT3B25: J181.3, U26.P13
OUT3B26: J188.3, U27.P13
OUT3B27: J195.3, U28.P13
OUT4: J3.1, U1.P11
OUT4B: J3.2, U1.P12
OUT4B1: J13.2, U2.P12
OUT4B2: J20.2, U3.P12
OUT4B3: J27.2, U4.P12
OUT4B4: J34.2, U5.P12
OUT4B5: J41.2, U6.P12
OUT4B6: J48.2, U7.P12
OUT4B7: J55.2, U8.P12
OUT4B8: J62.2, U9.P12
OUT4B9: J69.2, U10.P12
OUT4B10: J76.2, U11.P12
OUT4B11: J83.2, U12.P12
OUT4B12: J90.2, U13.P12
OUT4B13: J97.2, U14.P12
OUT4B14: J104.2, U15.P12
OUT4B15: J111.2, U16.P12
OUT4B16: J118.2, U17.P12
OUT4B17: J125.2, U18.P12
OUT4B18: J132.2, U19.P12
OUT4B19: J139.2, U20.P12
OUT4B20: J146.2, U21.P12
OUT4B21: J153.2, U22.P12
OUT4B22: J160.2, U23.P12
OUT4B23: J167.2, U24.P12
OUT4B24: J174.2, U25.P12
OUT4B25: J181.2, U26.P12
OUT4B26: J188.2, U27.P12
OUT4B27: J195.2, U28.P12
OUT5: J13.8, U2.P20
OUT6: J13.6, U2.P17
OUT7: J13.4, U2.P14
OUT8: J13.1, U2.P11
OUT9: J20.8, U3.P20
OUT10: J20.6, U3.P17
OUT11: J20.4, U3.P14
OUT12: J20.1, U3.P11
OUT13: J27.8, U4.P20
OUT14: J27.6, U4.P17
OUT15: J27.4, U4.P14
OUT16: J27.1, U4.P11
OUT17: J34.8, U5.P20
OUT18: J34.6, U5.P17
OUT19: J34.4, U5.P14
OUT20: J34.1, U5.P11
OUT21: J41.8, U6.P20
OUT22: J41.6, U6.P17
OUT23: J41.4, U6.P14
OUT24: J41.1, U6.P11
OUT25: J48.8, U7.P20
OUT26: J48.6, U7.P17
OUT27: J48.4, U7.P14
OUT28: J48.1, U7.P11
OUT29: J55.8, U8.P20
OUT30: J55.6, U8.P17
OUT31: J55.4, U8.P14
OUT32: J55.1, U8.P11
OUT33: J62.8, U9.P20
OUT34: J62.6, U9.P17
OUT35: J62.4, U9.P14
OUT36: J62.1, U9.P11
OUT37: J69.8, U10.P20
OUT38: J69.6, U10.P17
OUT39: J69.4, U10.P14
OUT40: J69.1, U10.P11
OUT41: J76.8, U11.P20
OUT42: J76.6, U11.P17
OUT43: J76.4, U11.P14
OUT44: J76.1, U11.P11
OUT45: J83.8, U12.P20
OUT46: J83.6, U12.P17
OUT47: J83.4, U12.P14
OUT48: J83.1, U12.P11
OUT49: J90.8, U13.P20
OUT50: J90.6, U13.P17
OUT51: J90.4, U13.P14
OUT52: J90.1, U13.P11
OUT53: J97.8, U14.P20
OUT54: J97.6, U14.P17
OUT55: J97.4, U14.P14
OUT56: J97.1, U14.P11
OUT57: J104.8, U15.P20
OUT58: J104.6, U15.P17
OUT59: J104.4, U15.P14
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
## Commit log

2019-08-22 Folder structure added
2019-08-26 Adds library with clock IC
2019-08-26 Initial Hardware Commit
2019-09-12 Routes board
2019-09-12 Adds silk, so much silk
2019-09-12 Adds a few (probably) unnecessary stitching vias
2019-09-13 Adds silk to jumpers and adds smaller diameter through holes for clock signals
2019-09-13 Adjusts via for better ground pour
2019-09-16 Minor adjustments to schematic
2019-09-16 Removes pulling SEL_I2CB line from ground, and instead leaves it floating
2019-09-16 Removes screw terminals in place of PTH header (with additional ground through holes)
    * Adds better silk that...just makes more sense
    * Adds ground vias to ground pad under IC
2019-09-16 Moves I2C header to align with bottom header
2019-09-17 Enlarges the silk on the bottom side labeling the clocks
2019-09-17 Updates README with all but description
2019-09-17 Updates crystal and 12pF parts
2019-09-19 Adds default address to schematic, moves design to 0,0 , updates right angle qwiic connector with value
2019-09-19 Panelizes NEO-M9N and cams gerbers
2019-09-19 Changes DRC to SparkFun Tight to ensure that JLCPCB could do it - parts were adjusted accordingly
2019-09-19 Adds new production files for update design with different DRC
2019-09-26 Update ferrite bead
2019-09-30 Updates crystal footprint, and fixes routing
2019-09-30 Moves SCL silk back to its' pin
2019-12-16 Radical change to design
    * Moved all parts besides crystal and IC to "bottom of board"
    * This allows for better routing of Clock signals
    * Adds 2.2Ohm series resistor to power rail
2020-01-14 Updates board with select jumper to enable select mode and fixes labels
    * Also swaps clock out 4 and 4B
2020-01-15 Improves ground plane pour, adds some more vias, updates packages of clock and crystal
2020-01-15 Checks DRC and fixes errors
2020-01-16 Fixes "SEL" text, adds second ground pour for clock lines isolate only, fixes power shorting through ferrite and resistor
2020-01-16 Fixes air wires, adds clock generator to eagle library, removes buzzard label folder
2020-01-17 Rotates Ferrite bead,
2020-01-17 Replace "SEL" silk - not sure where it went.
2020-01-17 Adds more info to schematic, removes old production files and unnecessary README's
2020-01-17 Adds Production Files for a 6x7 Panel
2020-01-17 Puts the aforementioned production files in the right folder.
2020-01-17 Replaces previous panel due to the Panelizer changing the DRC
2020-02-14 Removes buzzard labels, moves datasheet
2020-02-27 Updates README
2020-02-28 Update README.md
    Update tutorial link
2020-02-28 Create IDT_VC6E---RegProgGuide_MAU_20180830_Clock_Registers.pdf
    Add manufacturer's programming guide
